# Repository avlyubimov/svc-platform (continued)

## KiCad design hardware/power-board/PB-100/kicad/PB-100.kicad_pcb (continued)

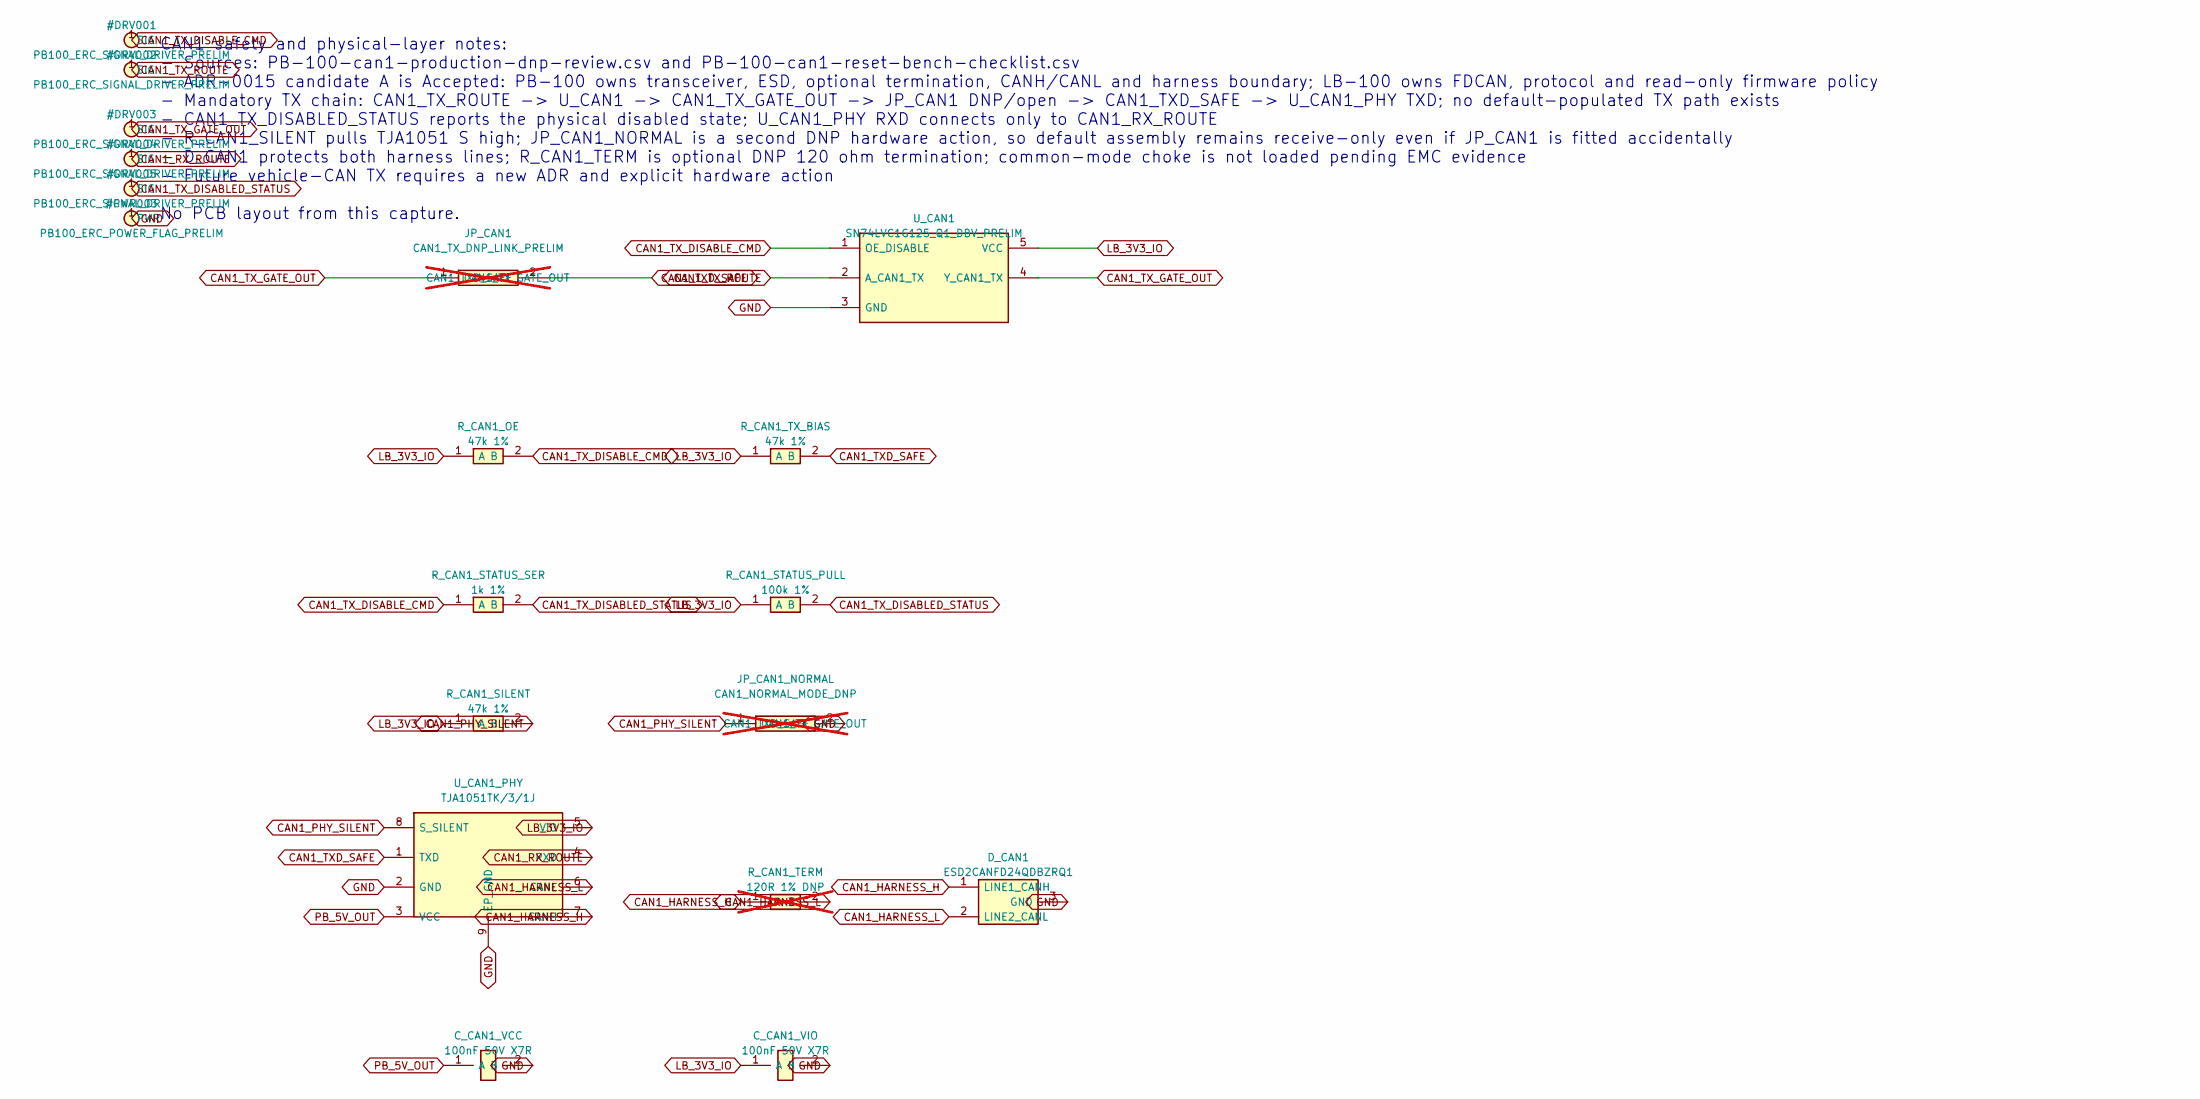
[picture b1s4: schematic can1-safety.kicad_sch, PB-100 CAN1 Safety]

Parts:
C_CAN1_VCC, C_CAN1_VIO: 100nF 50V X7R; C0402
D_CAN1: ESD2CANFD24QDBZRQ1; SOT-23-3_DBZ_TI
JP_CAN1: CAN1_TX_DNP_LINK_PRELIM; R0603_DNP_LINK_1608Metric; not fitted
JP_CAN1_NORMAL: CAN1_NORMAL_MODE_DNP; R0603_DNP_LINK_1608Metric; not fitted
R_CAN1_OE, R_CAN1_SILENT, R_CAN1_TX_BIAS: 47k 1%; R0402
R_CAN1_STATUS_PULL: 100k 1%; R0402
R_CAN1_STATUS_SER: 1k 1%; R0402
R_CAN1_TERM: 120R 1% DNP; R0603_DNP_LINK_1608Metric; not fitted
U_CAN1: SN74LVC1G125_Q1_DBV_PRELIM; SOT-23-5_DBV_TI
U_CAN1_PHY: TJA1051TK/3/1J; HVSON-8_L3.0-W3.0-P0.65-BL-EP

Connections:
CAN1_HARNESS_H: D_CAN1.1 (LINE1_CANH), R_CAN1_TERM.1 (A), U_CAN1_PHY.7 (CANH)
CAN1_HARNESS_L: D_CAN1.2 (LINE2_CANL), R_CAN1_TERM.2 (B), U_CAN1_PHY.6 (CANL)
CAN1_PHY_SILENT: JP_CAN1_NORMAL.1 (CAN1_TX_GATE_OUT), R_CAN1_SILENT.2 (B), U_CAN1_PHY.8 (S_SILENT)
CAN1_TXD_SAFE: JP_CAN1.2 (CAN1_TXD_SAFE), R_CAN1_TX_BIAS.2 (B), U_CAN1_PHY.1 (TXD)
LB_3V3_IO: C_CAN1_VIO.1 (A), R_CAN1_OE.1 (A), R_CAN1_SILENT.1 (A), R_CAN1_STATUS_PULL.1 (A), R_CAN1_TX_BIAS.1 (A), U_CAN1.5 (VCC), U_CAN1_PHY.5 (VIO); also elsewhere on the board
PB_5V_OUT: C_CAN1_VCC.1 (A), U_CAN1_PHY.3 (VCC); also elsewhere on the board

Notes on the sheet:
CAN1 safety and physical-layer notes: - Sources: PB-100-can1-production-dnp-review.csv and PB-100-can1-reset-bench-checklist.csv - ADR-0015 candidate A is Accepted: PB-100 owns transceiver, ESD, optional termination, CANH/CANL and harness boundary; LB-100 owns FDCAN, protocol and read-only firmware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

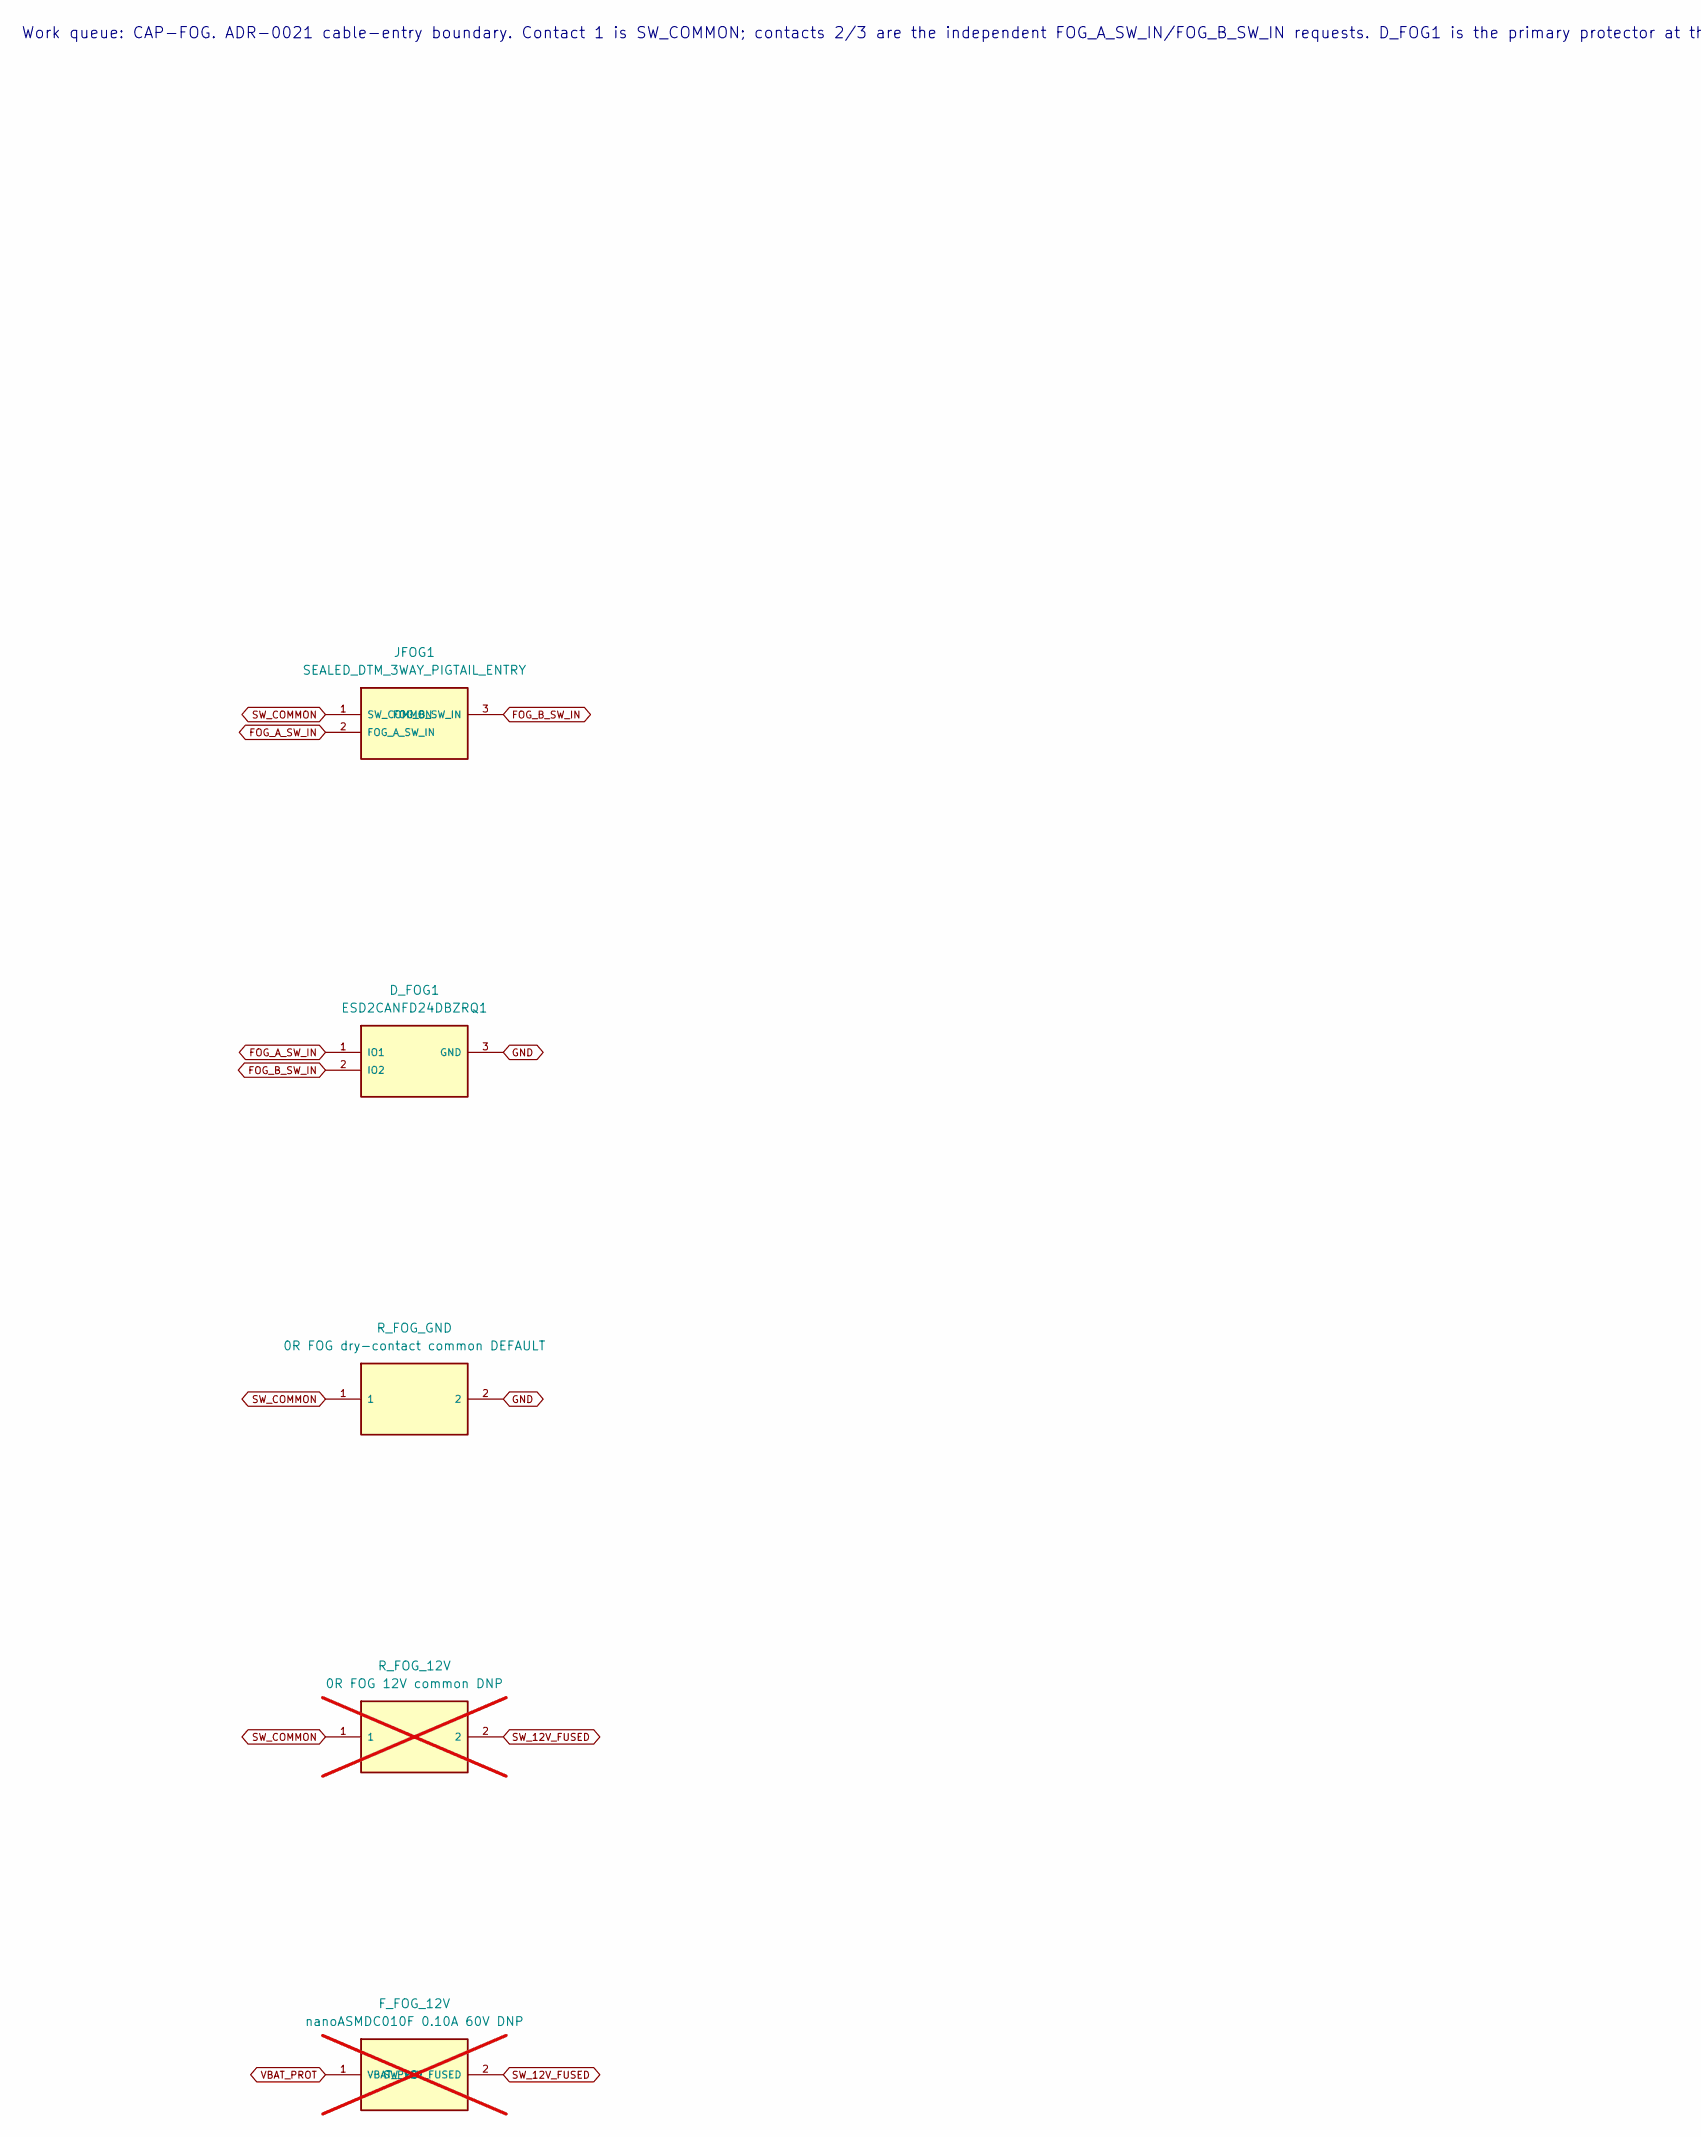
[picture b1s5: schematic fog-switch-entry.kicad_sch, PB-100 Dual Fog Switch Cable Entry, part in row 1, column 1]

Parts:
D_FOG1: ESD2CANFD24DBZRQ1; SOT-23-3_DBZ_TI
F_FOG_12V: nanoASMDC010F 0.10A 60V DNP; PPTC_1206_3216Metric; not fitted
JFOG1: SEALED_DTM_3WAY_PIGTAIL_ENTRY; FOG_PIGTAIL_1x03_P3.50mm
R_FOG_12V: 0R FOG 12V common DNP; R0603_DNP_LINK_1608Metric; not fitted
R_FOG_GND: 0R FOG dry-contact common DEFAULT; R0603_DNP_LINK_1608Metric

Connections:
SW_12V_FUSED: F_FOG_12V.2 (SW_12V_FUSED), R_FOG_12V.2
SW_COMMON: JFOG1.1 (SW_COMMON), R_FOG_12V.1, R_FOG_GND.1
VBAT_PROT: F_FOG_12V.1 (VBAT_PROT); also elsewhere on the board

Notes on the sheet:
Work queue: CAP-FOG. ADR-0021 cable-entry boundary. Contact 1 is SW_COMMON; contacts 2/3 are the independent FOG_A_SW_IN/FOG_B_SW_IN requests. D_FOG1 is the primary protector at the PB entry. R_FOG_GND is fitted for the default dry-contact assembly. R_FOG_12V and F_FOG_12V are mutually exclusive DN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

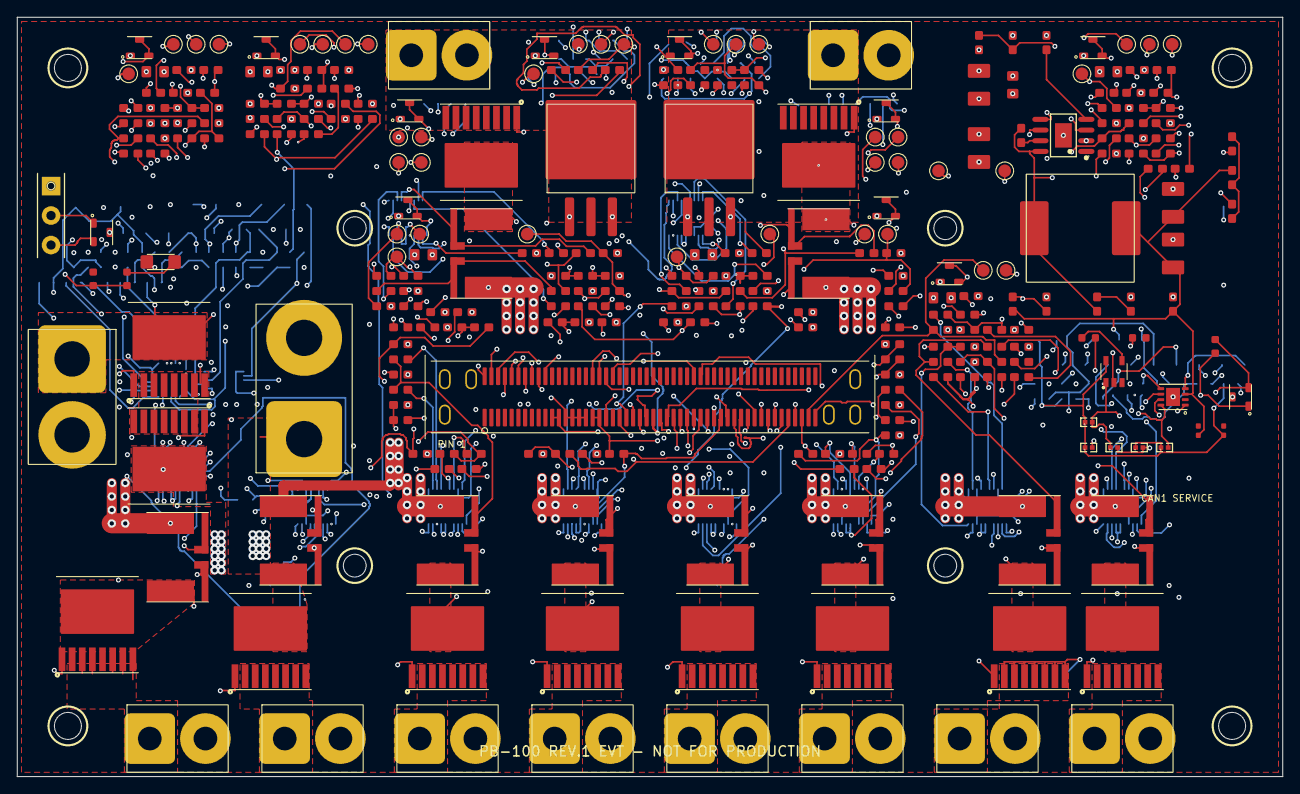
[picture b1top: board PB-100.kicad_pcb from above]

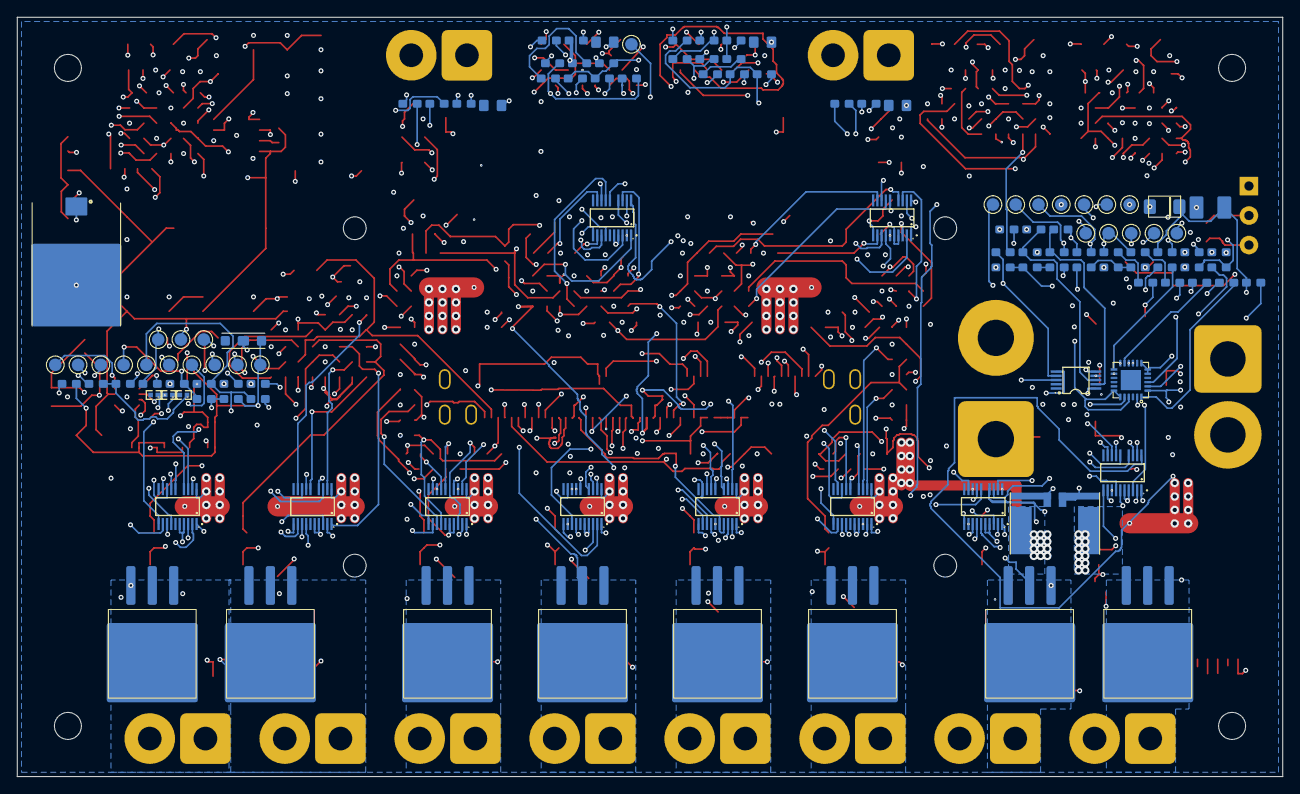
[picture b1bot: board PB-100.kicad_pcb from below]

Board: 8 copper layers, 150.0 x 90.0 mm, 422 parts (118 on the bottom side), 260 nets.

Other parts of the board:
H1, H2, H3, H4: LOCAL M3 NPTH; MountingHole_3.2mm
H5, H6, H7, H8: STACK M2.5 NPTH; MountingHole_2.7mm

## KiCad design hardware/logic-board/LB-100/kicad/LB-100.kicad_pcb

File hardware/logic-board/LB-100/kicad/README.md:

# LB-100 KiCad Project

Status: `EVT-FAB-AUTHORIZED`; connectivity-complete six-layer Rev.1 EVT layout

This directory contains the reviewed value-bearing LB-100 schematic,
project-local libraries and deterministically generated PCB.

The controlled `LB-100.kicad_pcb` contains all 104 schematic footprints, eight mounting
holes, the 100 mm x 70 mm outline, 2,274 routed segments, 409 standard
0.50/0.30 mm through vias and four GND zones. KiCad 10.0.4 refill DRC reports
zero errors and zero unconnected items; parity contains only H1-H8. Five
non-assembly pads provide E73 SWDIO, SWDCLK, reset, switched target reference
and GND recovery access.

The six-layer stack model is JLCPCB `JLC06161H-3313`. In2.Cu and In4.Cu are
solid GND reference planes, In1.Cu and In3.Cu carry signals, and the E73 rule
area covers every copper layer. The routing manifest is the source for board
generation; do not hand-edit generated copper.

Validation with KiCad 10.0.4:

```sh
python3 tools/validate_lb100_layout.py
```

The validator checks deterministic generation, schematic parity, route/via
counts, standard through-via construction, reference-plane exclusivity, USB
geometry and analytical impedance regression, VEML7700 disposition, the
six-layer E73 keepout and the exact reviewed non-electrical warning set.

Any EVT fabrication package must remain LB-only, marked
`LB-100 REV.1 EVT - NOT FOR PRODUCTION`, and must pass the supplier stackup,
impedance and DFM preflight before payment. PB-100 and the combined three-board
order remain `NO-GO`. Authorized LB manufacturing outputs are segregated under
`../manufacturing/evt-rev1/`; no assembly outputs are authorized.

## Source documents

- `../LB-100-layout-progress.md`
- `../LB-100-evt-fab-review-2026-07-22.md`
- `../LB-100-e73-antenna-keepout.md`
- `../LB-100-pcb-layout-start-checklist.csv`
- `../../../../production/board-order/three_board_layout_rules.md`
- `../../../../docs/adr/ADR-0014-lb-fb-baseline-requirements.md`

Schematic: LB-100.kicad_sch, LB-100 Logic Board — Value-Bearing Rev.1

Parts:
C1: 1uF 10V X7R; R_C_0603_1608Metric
C2, C4, C28: 1uF 6.3V X7R; R_C_0603_1608Metric
C3: 10uF 6.3V X7R; R_C_0805_2012Metric
C5, C8, C15, C16, C17, C18, C19, C20, C21, C22, C23, C24, C25, C26, C27, C29, C30: 100nF 6.3V X7R; R_C_0603_1608Metric
C6, C7: 2.2uF 6.3V X7R; R_C_0603_1608Metric
C9, C10: 18pF 50V C0G; R_C_0603_1608Metric
C11, C12: 8.2pF 50V C0G; R_C_0603_1608Metric
C13, C14: 1nF 50V C0G; R_C_0603_1608Metric
C31: 100nF 6.3V X7R BMI270 VDDIO; R_C_0603_1608Metric
C32: 100nF 6.3V X7R U15; R_C_0603_1608Metric
C33: 100nF 6.3V X7R U16; R_C_0603_1608Metric
C34: 100nF 6.3V X7R U17; R_C_0603_1608Metric
C35: 47nF 50V X7R FOG_A filter; R_C_0603_1608Metric
C36: 47nF 50V X7R FOG_B filter; R_C_0603_1608Metric
C37: 100nF 6.3V X7R U18; R_C_0603_1608Metric
C38: 100nF 6.3V X7R U19; R_C_0603_1608Metric
D19, D20: BZT52H-B4V3-Q; SOD-123F_L2.6-W1.6
FB1: 600R@100MHz 0.2A; R_C_0603_1608Metric
JBT1: BACKUP_BATTERY_2V3_TO_3V6_DNP; PinHeader_1x02_P2.54mm_Vertical; not fitted
JDBG1: SWD_2x3_1.27mm; PinHeader_2x03_P1.27mm_Vertical
JFB1: AFC07-S24ECA-00; FPC-SMD_AFC07-S24ECA-00
JPB1: FX18-100S-0.8SV10; FX18-100S-0.8SV10_Hirose
JSD1: TF-015; TF-SMD_TF-015
Q18, Q19: BC847BQ-7-F 12V OPTION; SOT-23-3_DBZ_TI; not fitted
R1: 100k 1%; R_C_0603_1608Metric
R2, R3, R13, R14, R15, R16: 0R; R_C_0603_1608Metric
R4, R5, R12: 10k 1%; R_C_0603_1608Metric
R6, R7: 2.2k 1%; R_C_0603_1608Metric
R8: 4.7k 1%; R_C_0603_1608Metric
R9: 10k 1% switched reset pull-up; R_C_0603_1608Metric
R10, R11: 47k 1%; R_C_0603_1608Metric
R17: 0R single-point analog return; R_C_0603_1608Metric
R18, R19: 22k 1% switched UART idle clamp; R_C_0603_1608Metric
R20, R22: 100k 1% MCU UART idle pull-up; R_C_0603_1608Metric
R21: 100k 1% reset default assert; R_C_0603_1608Metric
R23: 4.7k 1% FOG_A dry-contact series; R_C_0603_1608Metric
R24: 47k 1% FOG_A 12V base DNP; R_C_0603_1608Metric; not fitted
R25: 100k 1% FOG_A base pull-down DNP; R_C_0603_1608Metric; not fitted
R26: 47k 1% FOG_A pull-up; R_C_0603_1608Metric
R27: 4.7k 1% FOG_B dry-contact series; R_C_0603_1608Metric
R28: 47k 1% FOG_B 12V base DNP; R_C_0603_1608Metric; not fitted
R29: 100k 1% FOG_B base pull-down DNP; R_C_0603_1608Metric; not fitted
R30: 47k 1% FOG_B pull-up; R_C_0603_1608Metric
TP1: E73_SWDIO; TestPoint_SMD_1.2mm
TP2: E73_SWDCLK; TestPoint_SMD_1.2mm
TP3: BLE_RESET_N; TestPoint_SMD_1.2mm
TP4: RADIO_SENSOR_3V3; TestPoint_SMD_1.2mm
TP5: GND; TestPoint_SMD_1.2mm
U1: STM32H563VIT6; LQFP-100_L14.0-W14.0-P0.50-LS16.0-BL
U2: XC6220B331MR-G; SOT-25_L3.0-W1.6-P0.95-LS2.8-TL
U3: TCA9539QPWRQ1; TSSOP-24_4.4x7.8mm_P0.65mm
U4: TJA1051TK/3,118; HVSON-8_L3.0-W3.0-P0.65-BL-EP; not fitted
U5: TJA1021T/20/CM,118; SOIC-8_L4.9-W3.9-P1.27-LS6.0-BL; not fitted
U6: SP3485EN-L/TR; SOIC-8_L5.0-W4.0-P1.27-LS6.0-BL; not fitted
U7: E73-2G4M08S1C; WIRELM-SMD_E73-2G4M08S1C
U8: FM24CL64B-GTR; SOIC-8_L4.9-W3.9-P1.27-LS6.0-BL
U9: DS3231MZ+TRL; SOIC-8_L4.9-W3.9-P1.27-LS6.0-BL
U10: BMI270; LGA-14_L3.0-W2.5-P0.50-BR
U11: VEML7700-TT; SENSOR-SMD_EML7700-TT
U12, U13: TPS22918TDBVRQ1; SOT-23-6_L2.9-W1.6-P0.95-LS2.8-BL
U14, U18, U19: SN74LVC1G17QDBVRQ1; SOT-25_L3.0-W1.6-P0.95-LS2.8-TL
U15, U16, U17: SN74LVC1G125QDBVRQ1; SOT-25_L3.0-W1.6-P0.95-LS2.8-TL
Y1: ABM8AIG-25.000MHZ-12-2Z-T3; Crystal_SMD_3225-4Pin
Y2: ABS07AIG-32.768kHz-7-T; Crystal_SMD_3215-2Pin

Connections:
ADC_REF: C28.1, C29.1, JPB1.66 (ADC_REF), R16.2, U1.21 (VREF+)
AGND: C4.2, C5.2, C28.2, C29.2, JPB1.11 (AGND), JPB1.12 (AGND), R17.1, U1.19 (VSSA), U1.20 (VREF-)
BACKUP_AON: JBT1.1 (BACKUP_AON), U9.6 (VBAT)
BLE_RESET_N: R9.2, TP3.1 (BLE_RESET_N), U7.26 (RESET), U17.4 (Y)
BLE_RESET_N_MCU: R21.1, U1.97 (PE0), U17.2 (A)
BLE_UART_RX_MODULE: R18.1, U7.22 (P0.07), U15.4 (Y)
BLE_UART_TX_MODULE: R19.1, U7.20 (P0.12), U16.2 (A)
BOOT0: R5.1, U1.94 (BOOT0)
CAN1_RX_ROUTE: JPB1.69 (CAN1_RX_ROUTE), U1.95 (PB8)
CAN1_TX_DISABLED_STATUS: JPB1.68 (CAN1_TX_DISABLED_STATUS), U1.58 (PD11)
CAN1_TX_DISABLE_CMD: JPB1.67 (CAN1_TX_DISABLE_CMD), U1.85 (PD4)
CAN1_TX_ROUTE: JPB1.70 (CAN1_TX_ROUTE), U1.96 (PB9)
CAN2_RX_ROUTE: JPB1.71 (CAN2_RX_ROUTE), U1.51 (PB12), U4.4 (RXD)
CAN2_TX_ROUTE: JPB1.72 (CAN2_TX_ROUTE), U1.52 (PB13), U4.1 (TXD)
CH_LED_1: JFB1.10 (CH_LED_1), U3.4 (P00)
CH_LED_2: JFB1.11 (CH_LED_2), U3.5 (P01)
CH_LED_3: JFB1.12 (CH_LED_3), U3.6 (P02)
CH_LED_4: JFB1.13 (CH_LED_4), U3.7 (P03)
CH_LED_5: JFB1.14 (CH_LED_5), U3.8 (P04)
CH_LED_6: JFB1.15 (CH_LED_6), U3.9 (P05)
CH_LED_7: JFB1.16 (CH_LED_7), U3.10 (P06)
CH_LED_8: JFB1.17 (CH_LED_8), U3.11 (P07)
CH_LED_9: JFB1.18 (CH_LED_9), U3.13 (P10)
CH_LED_10: JFB1.19 (CH_LED_10), U3.14 (P11)
E73_SWDCLK: TP2.1 (E73_SWDCLK), U7.39 (SWDCLK)
E73_SWDIO: TP1.1 (E73_SWDIO), U7.37 (SWDIO)
EXT_5V_EN: JPB1.84 (EXT_5V_EN), U1.69 (PA10)
EXT_ADC1: JPB1.80 (EXT_ADC1), U1.64 (PC7)
EXT_ADC2: JPB1.81 (EXT_ADC2), U1.65 (PC8)
FB_3V3_OR_IO: JFB1.2 (FB_3V3_OR_IO), R3.2
FOG_A_12V_BASE: Q18.1 (B), R24.2, R25.1
FOG_A_FILTERED: C35.1, D19.1 (K), Q18.3 (C), R23.2, R26.2, U18.2 (A)
FOG_A_SW_IN: JPB1.82 (FOG_A_SW_IN), R23.1, R24.1
FOG_A_SW_IN_MCU: U1.67 (PA8), U18.4 (Y)
FOG_B_12V_BASE: Q19.1 (B), R28.2, R29.1
FOG_B_FILTERED: C36.1, D20.1 (K), Q19.3 (C), R27.2, R30.2, U19.2 (A)
FOG_B_SW_IN: JPB1.83 (FOG_B_SW_IN), R27.1, R28.1
FOG_B_SW_IN_MCU: U1.68 (PA9), U19.4 (Y)
GND: C1.2, C2.2, C3.2, C6.2, C7.2, C8.2, C9.2, C10.2, C11.2, C12.2, C13.2, C14.2, C15.2, C16.2, C17.2, C18.2, C19.2, C20.2, C21.2, C22.2, C23.2, C24.2, C25.2, C26.2, C27.2, C30.2, C31.2, C32.2, C33.2, C34.2, C35.2, C36.2, C37.2, C38.2, D19.2 (A), D20.2 (A), JBT1.2 (GND), JDBG1.3 (GND), JDBG1.5 (GND), JFB1.1 (GND), JFB1.3 (GND), JFB1.25 (SHIELD_A), JFB1.26 (SHIELD_B), JPB1.1 (GND), JPB1.2 (GND), JPB1.3 (GND), JPB1.4 (GND), JPB1.5 (GND), JPB1.6 (GND), JPB1.7 (GND), JPB1.8 (GND), JPB1.9 (GND), JPB1.10 (GND), JPB1.MF_A_PIN1_51_END, JPB1.MF_A_PIN50_100_END, JPB1.MF_B_PIN1_51_END, JPB1.MF_B_PIN50_100_END, JSD1.6 (VSS), JSD1.10 (SHELL1), JSD1.11 (SHELL2), JSD1.12 (SHELL3), JSD1.13 (SHELL4), Q18.2 (E), Q19.2 (E), R1.2, R5.2, R17.2, R21.2, R25.2, R29.2, TP5.1 (GND), U1.10 (VSS), U1.27 (VSS), U1.49 (VSS), U1.74 (VSS), U1.99 (VSS), U2.2 (VSS), U3.2 (A1), U3.12 (GND), U3.21 (A0), U4.2 (GND), U4.9 (EP), U5.2 (SLP_N), U5.5 (GND), U6.5 (GND), U7.5 (GND), U7.21 (GND), U7.24 (GND), U8.1 (A0), U8.2 (A1), U8.3 (A2), U8.4 (VSS), U8.7 (WP), U9.5 (GND), U10.1 (SDO), U10.6 (GNDIO), U10.7 (GND), U11.3 (GND), U12.2 (GND), U13.2 (GND), U14.3 (GND), U15.1 (OE_N), U15.3 (GND), U16.1 (OE_N), U16.3 (GND), U17.1 (OE_N), U17.3 (GND), U18.3 (GND), U19.3 (GND), Y1.2 (GND1), Y1.4 (GND2)
IIN_SENSE: JPB1.52 (IIN_SENSE), U1.32 (PA7)
IMU_INT1: U3.18 (P15), U10.4 (INT1)
IOX_INT_N: R8.2, U1.54 (PB15), U3.1 (INT_N)
LB_3V3_ANALOG: C4.1, C5.1, FB1.2, R16.1, U1.22 (VDDA)
LB_3V3_IO: C30.1, C31.1, C37.1, C38.1, JPB1.17 (LB_3V3_IO), JPB1.18 (LB_3V3_IO), R2.2, R6.1, R7.1, R26.1, R30.1, U10.5 (VDDIO), U10.12 (CSB), U11.2 (VDD), U14.5 (VCC), U18.5 (VCC), U19.5 (VCC)
LB_3V3_MAIN: C2.1, C3.1, C15.1, C16.1, C17.1, C18.1, C19.1, C20.1, C21.1, FB1.1, JDBG1.1 (VTREF), R2.1, R3.1, R4.1, R8.1, R20.1, R22.1, U1.6 (VBAT), U1.11 (VDD), U1.28 (VDD), U1.50 (VDD), U1.73 (VDDUSB), U1.75 (VDD), U1.100 (VDD), U2.5 (VOUT), U3.24 (VCC), U4.5 (VIO), U4.8 (S), U5.3 (WAKE_N), U6.8 (VCC), U8.8 (VDD), U9.2 (VCC), U12.1 (VIN), U13.1 (VIN)
LIN_RX: JPB1.74 (LIN_RX), U1.87 (PD6), U5.1 (RXD)
LIN_TX: JPB1.73 (LIN_TX), U1.86 (PD5), U5.4 (TXD)
MCU_HSE_IN: C9.1, U1.12 (PH0-OSC_IN), Y1.1 (XIN)
MCU_HSE_OUT: C10.1, U1.13 (PH1-OSC_OUT), Y1.3 (XOUT)
MCU_LSE_IN: C11.1, U1.8 (PC14-OSC32_IN), Y2.1 (XIN)
MCU_LSE_OUT: C12.1, U1.9 (PC15-OSC32_OUT), Y2.2 (XOUT)
MICROSD_3V3: C26.1, C27.1, JSD1.4 (VDD), R10.1, R11.1, R12.1, U12.5 (QOD), U12.6 (VOUT)
MICROSD_3V3_CT: C13.1, U12.4 (CT)
MICROSD_CARD_DETECT: JSD1.9 (CARD_DETECT), U3.17 (P14)
MICROSD_CS_N: JSD1.2 (CD_DAT3), R12.2, U1.80 (PC12)
MICROSD_DAT1: JSD1.8 (DAT1), R10.2
MICROSD_DAT2: JSD1.1 (DAT2), R11.2
MICROSD_PWR_EN: U1.81 (PD0), U12.3 (ON)
NRST: C8.1, R4.2, R15.1, U1.14 (NRST), U3.3 (RESET_N), U9.4 (RST_N)
OLED_RST_OR_INT_DNP: JFB1.24 (OLED_RST_OR_INT_DNP), U3.20 (P17)
OLED_SCL: JFB1.22 (OLED_SCL), R13.2
OLED_SDA: JFB1.23 (OLED_SDA), R14.2
OUT1_CTL: JPB1.21 (OUT1_CTL), U1.4 (PE5)
OUT1_FLT: JPB1.31 (OUT1_FLT), U1.1 (PE2)
OUT1_IMON: JPB1.41 (OUT1_IMON), U1.15 (PC0)
OUT2_CTL: JPB1.22 (OUT2_CTL), U1.5 (PE6)
OUT2_FLT: JPB1.32 (OUT2_FLT), U1.2 (PE3)
OUT2_IMON: JPB1.42 (OUT2_IMON), U1.16 (PC1)
OUT3_CTL: JPB1.23 (OUT3_CTL), U1.40 (PE9)
OUT3_FLT: JPB1.33 (OUT3_FLT), U1.3 (PE4)
OUT3_IMON: JPB1.43 (OUT3_IMON), U1.17 (PC2)
OUT4_CTL: JPB1.24 (OUT4_CTL), U1.42 (PE11)
OUT4_FLT: JPB1.34 (OUT4_FLT), U1.38 (PE7)
OUT4_IMON: JPB1.44 (OUT4_IMON), U1.18 (PC3)
OUT5_CTL: JPB1.25 (OUT5_CTL), U1.44 (PE13)
OUT5_FLT: JPB1.35 (OUT5_FLT), U1.39 (PE8)
OUT5_IMON: JPB1.45 (OUT5_IMON), U1.23 (PA0)
OUT6_CTL: JPB1.26 (OUT6_CTL), U1.45 (PE14)
OUT6_FLT: JPB1.36 (OUT6_FLT), U1.41 (PE10)
OUT6_IMON: JPB1.46 (OUT6_IMON), U1.24 (PA1)
OUT7_CTL: JPB1.27 (OUT7_CTL), U1.59 (PD12)
OUT7_FLT: JPB1.37 (OUT7_FLT), U1.43 (PE12)
OUT7_IMON: JPB1.47 (OUT7_IMON), U1.25 (PA2)
OUT8_CTL: JPB1.28 (OUT8_CTL), U1.60 (PD13)
OUT8_FLT: JPB1.38 (OUT8_FLT), U1.46 (PE15)
OUT8_IMON: JPB1.48 (OUT8_IMON), U1.26 (PA3)
OUT9_CTL: JPB1.29 (OUT9_CTL), U1.61 (PD14)
OUT9_FLT: JPB1.39 (OUT9_FLT), U1.63 (PC6)
OUT9_IMON: JPB1.49 (OUT9_IMON), U1.29 (PA4)
OUT10_CTL: JPB1.30 (OUT10_CTL), U1.62 (PD15)
OUT10_FLT: JPB1.40 (OUT10_FLT), U1.66 (PC9)
OUT10_IMON: JPB1.50 (OUT10_IMON), U1.30 (PA5)
PB_5V_OUT: C1.1, JPB1.13 (PB_5V_OUT), JPB1.14 (PB_5V_OUT), JPB1.15 (PB_5V_OUT), JPB1.16 (PB_5V_OUT), U2.1 (VIN), U4.3 (VCC)
PB_FAULT: JPB1.56 (PB_FAULT), U1.84 (PD3)
PB_I2C_INT: JPB1.59 (PB_I2C_INT), U1.47 (PB10)
PB_I2C_SCL: JPB1.57 (PB_I2C_SCL), R6.2, R13.1, U1.92 (PB6), U3.22 (SCL), U8.6 (SCL), U9.8 (SCL), U10.13 (SCL), U11.1 (SCL)
PB_I2C_SDA: JPB1.58 (PB_I2C_SDA), R7.2, R14.1, U1.93 (PB7), U3.23 (SDA), U8.5 (SDA), U9.7 (SDA), U10.14 (SDA), U11.4 (SDA)
PB_ID_ADC: JPB1.60 (PB_ID_ADC), U1.36 (PB1)
PB_PWR_GOOD: JPB1.19 (PB_PWR_GOOD), R1.1, U1.83 (PD2), U2.3 (CE)
PB_SPI_CS0: JPB1.64 (PB_SPI_CS0), U1.77 (PA15)
PB_SPI_CS1: JPB1.65 (PB_SPI_CS1), U1.37 (PB2)
PB_SPI_MISO: JPB1.62 (PB_SPI_MISO), JSD1.7 (DAT0), U1.90 (PB4)
PB_SPI_MOSI: JPB1.63 (PB_SPI_MOSI), JSD1.3 (CMD), U1.91 (PB5)
PB_SPI_SCK: JDBG1.6 (SWO), JPB1.61 (PB_SPI_SCK), JSD1.5 (CLK), U1.89 (PB3-SWO)
PB_WAKE_REQ: JPB1.20 (PB_WAKE_REQ), U1.7 (PC13)
RADIO_SENSOR_3V3: C22.1, C23.1, C24.1, C25.1, C32.1, C33.1, C34.1, R9.1, R18.2, R19.2, TP4.1 (RADIO_SENSOR_3V3), U7.19 (VCC), U10.8 (VDD), U13.5 (QOD), U13.6 (VOUT), U15.5 (VCC), U16.5 (VCC), U17.5 (VCC)
RADIO_SENSOR_3V3_CT: C14.1, U13.4 (CT)
RADIO_SENSOR_EN: U1.82 (PD1), U13.3 (ON)
RESET_BTN: JFB1.21 (RESET_BTN), R15.2
RS485_DE: JPB1.75 (RS485_DE), U1.53 (PB14), U6.2 (RE_N), U6.3 (DE)
RS485_RX: JPB1.76 (RS485_RX), U1.56 (PD9), U6.1 (RO)
RS485_TX: JPB1.77 (RS485_TX), U1.55 (PD8), U6.4 (DI)
RTC_INT_N: U3.19 (P16), U9.3 (INT_SQW_N)
SERVICE_BTN: JFB1.20 (SERVICE_BTN), U3.16 (P13)
STATUS_RGB_DATA: JFB1.9 (STATUS_RGB_DATA), U1.88 (PD7)
SWCLK: JDBG1.4 (SWCLK), U1.76 (PA14-SWCLK)
SWDIO: JDBG1.2 (SWDIO), U1.72 (PA13-SWDIO)
TEMP_PCB: JPB1.53 (TEMP_PCB), U1.33 (PC4)
TEMP_PWR_A: JPB1.54 (TEMP_PWR_A), U1.34 (PC5)
TEMP_PWR_B: JPB1.55 (TEMP_PWR_B), U1.35 (PB0)
UART_RX: JPB1.79 (UART_RX), R20.2, U1.79 (PC11), U16.4 (Y)
UART_TX: JPB1.78 (UART_TX), R22.2, U1.78 (PC10), U15.2 (A)
USB_CC1: JFB1.6 (USB_CC1)
USB_CC2: JFB1.7 (USB_CC2)
USB_D_N: JFB1.5 (USB_D_N), U1.70 (PA11-USB_DM)
USB_D_P: JFB1.4 (USB_D_P), U1.71 (PA12-USB_DP)
USB_VBUS_DETECT_RAW: JFB1.8 (USB_VBUS_DETECT_RAW), U14.2 (A)
USB_VBUS_PRESENT: U1.57 (PD10), U14.4 (Y)
VBAT_SENSE: JPB1.51 (VBAT_SENSE), U1.31 (PA6)
VCAP1: C6.1, U1.48 (VCAP1)
VCAP2: C7.1, U1.98 (VCAP2)

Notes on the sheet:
LB-100 reviewed value-bearing Rev.1 capture. STM32H563VIT6 LQFP100; exact ST package positions; JPB1 100 signals plus four GND MF circuits; PB_5V_OUT 500 mA allocation with reviewed 229.2 mA sustained and 381.2 mA service-peak budgets including FB-100 worst-case indication; ADR-0015 CAN1 FDCAN/read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

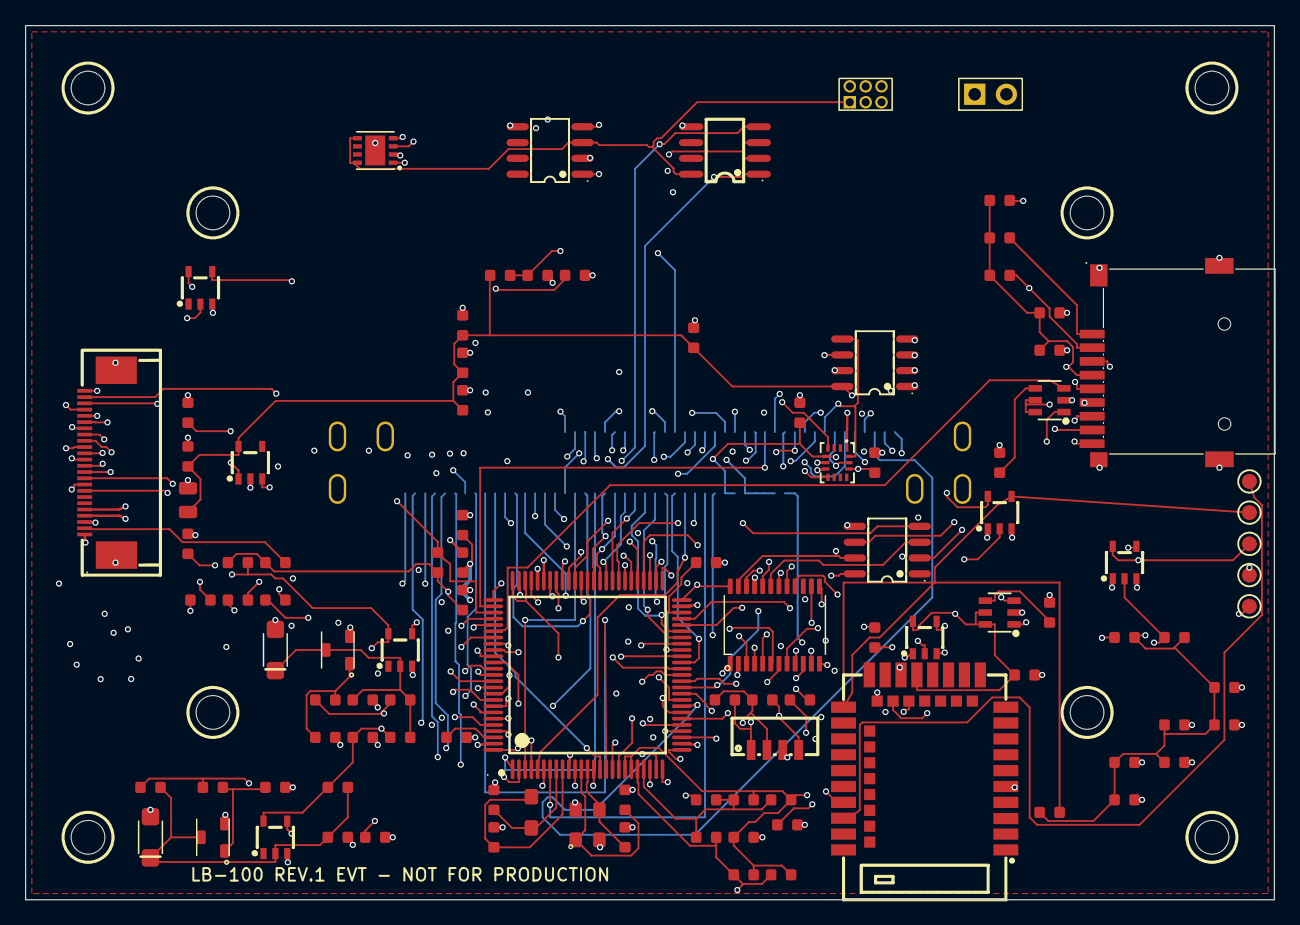
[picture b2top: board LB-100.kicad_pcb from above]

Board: 6 copper layers, 100.0 x 70.0 mm, 112 parts (1 on the bottom side), 129 nets.

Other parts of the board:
H1, H2, H3, H4: LOCAL M2.5 NPTH; MountingHole_2.7mm_M2.5
H5, H6, H7, H8: STACK M2.5 NPTH; MountingHole_2.7mm_M2.5

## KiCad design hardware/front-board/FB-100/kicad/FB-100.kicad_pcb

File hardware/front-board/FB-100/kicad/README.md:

# FB-100 KiCad Project

Status: `EVT-LAYOUT-AUTHORIZED`; connectivity routing complete; fab review open

This directory contains the reviewed value-bearing FB-100 KiCad schematic and
project-local symbol/footprint libraries.

The controlled `FB-100.kicad_pcb` placement and routing are generated from the frozen
44-component schematic and project-local footprints. Mechanical-envelope and
USB/no-back-power inputs are applied. The route manifest contains 457 segments,
48 vias and four filled GND zones with zero refilled DRC or unconnected findings.
USB stack geometry, analytical impedance/skew and transition return-via checks
are automated. Supplier field-solver confirmation, physical JFB1 cable/latch
fit, enclosure integration and final assembly DFM remain open. There are no
manufacturing outputs: Gerbers, drills, pick-place files, BOM/CPL order
packages, zipped fabrication packages, and board orders remain blocked until
the later prototype/production gates close.

Release boundary: no manufacturing outputs are authorized.

## Source Documents

- `../FB-100-requirements.md`
- `../FB-100-schematic-freeze-checklist.md`
- `../FB-100-pcb-layout-start-checklist.csv`
- `../FB-100-footprint-binding-inventory.csv`
- `../FB-100-footprint-binding-closeout.csv`
- `../FB-100-footprint-binding-closeout.md`
- `../FB-100-mechanical-envelope-inventory.csv`
- `../FB-100-mechanical-layout-inputs.csv`
- `../FB-100-usb-no-back-power-layout-rules.csv`
- `../FB-100-board-release-blocker-register.csv`
- `../../../../production/board-order/three_board_footprint_binding_status.csv`
- `../../../../production/board-order/three_board_mechanical_envelope_status.csv`
- `../../../logic-board/LB-100/LB-100-requirements.md`
- `../../../../docs/adr/ADR-0014-lb-fb-baseline-requirements.md`

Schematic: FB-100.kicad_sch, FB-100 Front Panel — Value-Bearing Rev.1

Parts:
C1: 100nF 16V X7R 10%; R_C_0603_1608Metric
C2: 1nF 1kV C0G; R_C_0603_1608Metric
C3, C4, C5: 1uF 6.3V X7R; R_C_0603_1608Metric
C6, C7: 100nF 6.3V X7R; R_C_0603_1608Metric
D1: USBLC6-2SC6; SOT-23-6_L2.9-W1.6-P0.95-LS2.8-BL
D2: 19-237/R6GHBHC-A01/2T; LED-ARRAY-SMD_4P-L1.6-W1.6-BL_1
D3, D4, D5, D6, D7, D8, D9, D10, D11, D12: KT-0805Y; LED0805-R-RD
J1: USB4105-GF-A; TYPE-C-SMD_SBC-160S1A-20-S412
J2: SSD1306_I2C_MODULE_DNP; PinHeader_1x04_P2.54mm_Vertical; not fitted
JFB1: AFC07-S24ECA-00; FPC-SMD_AFC07-S24ECA-00
R1, R2, R3, R4, R5, R6, R7, R8, R9, R10: 1k 1%; R_C_0603_1608Metric
R11, R12: 5.1k 1%; R_C_0603_1608Metric
R13: 3.9k 1% current limit; R_C_0603_1608Metric
R14: 15k 1% defined pulldown; R_C_0603_1608Metric
R15: 1M 1%; R_C_0603_1608Metric
R16: 35.7k 1%; R_C_0603_1608Metric
R17, R18: 10k 1%; R_C_0603_1608Metric
R19: 100k 1%; R_C_0603_1608Metric
SW1: EVPBB4A9B000 SERVICE; KEY-SMD_L2.6-W1.6-P0.75-LS3.0
SW2: EVPBB4A9B000 RESET; KEY-SMD_L2.6-W1.6-P0.75-LS3.0
U1: LTC3212EDDB#TRPBF; DFN-12-1EP_2x3mm_P0.45mm

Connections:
CH_LED_1: D3.2 (K), JFB1.10 (CH_LED_1)
CH_LED_1_A: D3.1 (A), R1.2
CH_LED_2: D4.2 (K), JFB1.11 (CH_LED_2)
CH_LED_2_A: D4.1 (A), R2.2
CH_LED_3: D5.2 (K), JFB1.12 (CH_LED_3)
CH_LED_3_A: D5.1 (A), R3.2
CH_LED_4: D6.2 (K), JFB1.13 (CH_LED_4)
CH_LED_4_A: D6.1 (A), R4.2
CH_LED_5: D7.2 (K), JFB1.14 (CH_LED_5)
CH_LED_5_A: D7.1 (A), R5.2
CH_LED_6: D8.2 (K), JFB1.15 (CH_LED_6)
CH_LED_6_A: D8.1 (A), R6.2
CH_LED_7: D9.2 (K), JFB1.16 (CH_LED_7)
CH_LED_7_A: D9.1 (A), R7.2
CH_LED_8: D10.2 (K), JFB1.17 (CH_LED_8)
CH_LED_8_A: D10.1 (A), R8.2
CH_LED_9: D11.2 (K), JFB1.18 (CH_LED_9)
CH_LED_9_A: D11.1 (A), R9.2
CH_LED_10: D12.2 (K), JFB1.19 (CH_LED_10)
CH_LED_10_A: D12.1 (A), R10.2
FB_3V3_OR_IO: C3.1, J2.2 (VCC), JFB1.2 (FB_3V3_OR_IO), R1.1, R2.1, R3.1, R4.1, R5.1, R6.1, R7.1, R8.1, R9.1, R10.1, R17.1, R18.1, U1.4 (ISETB), U1.5 (ISETR), U1.12 (VIN)
GND: C1.2, C2.2, C3.2, C5.2, C6.2, C7.2, D1.2 (GND), J1.A1 (GND), J1.A12 (GND), J1.B1 (GND), J1.B12 (GND), J2.1 (GND), JFB1.1 (GND), JFB1.3 (GND), JFB1.25 (SHIELD_A), JFB1.26 (SHIELD_B), R11.2, R12.2, R14.2, R15.2, R16.2, R19.2, SW1.B, SW1.B1, SW2.B, SW2.B1, U1.10 (GND), U1.13 (EP)
OLED_RST_OR_INT_DNP: JFB1.24 (OLED_RST_OR_INT_DNP), R19.1
OLED_SCL: J2.3 (SCL), JFB1.22 (OLED_SCL)
OLED_SDA: J2.4 (SDA), JFB1.23 (OLED_SDA)
RESET_BTN: C7.1, JFB1.21 (RESET_BTN), R18.2, SW2.A, SW2.A1
RGB_B_K: D2.4 (BLUE_K), U1.9 (LEDB)
RGB_CM: C4.2, U1.11 (CM)
RGB_CP: C4.1, U1.1 (CP)
RGB_G_K: D2.3 (GREEN_K), U1.7 (LEDG)
RGB_ISETG: R16.1, U1.6 (ISETG)
RGB_LED_ANODE: C5.1, D2.1 (COMMON_ANODE), U1.2 (CPO)
RGB_R_K: D2.2 (RED_K), U1.8 (LEDR)
SERVICE_BTN: C6.1, JFB1.20 (SERVICE_BTN), R17.2, SW1.A, SW1.A1
STATUS_RGB_DATA: JFB1.9 (STATUS_RGB_DATA), U1.3 (LEDEN)
USB_CC1: J1.A5 (CC1), JFB1.6 (USB_CC1), R11.1
USB_CC2: J1.B5 (CC2), JFB1.7 (USB_CC2), R12.1
USB_D_N: D1.4 (I_O2_OUT), JFB1.5 (USB_D_N)
USB_D_N_CONN: D1.3 (I_O2_IN), J1.A7 (D-), J1.B7 (D-)
USB_D_P: D1.6 (I_O1_OUT), JFB1.4 (USB_D_P)
USB_D_P_CONN: D1.1 (I_O1_IN), J1.A6 (D+), J1.B6 (D+)
USB_SHIELD: C2.1, J1.1 (SHIELD1), J1.2 (SHIELD2), J1.3 (SHIELD3), J1.4 (SHIELD4), R15.1
USB_VBUS: D1.5 (VBUS), J1.A4 (VBUS), J1.A9 (VBUS), J1.B4 (VBUS), J1.B9 (VBUS), R13.1
USB_VBUS_DETECT_RAW: C1.1, JFB1.8 (USB_VBUS_DETECT_RAW), R13.2, R14.1

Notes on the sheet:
FB-100 reviewed value-bearing Rev.1 capture. USB-C is USB2 device-only with two 5.1k Rd resistors, USBLC6-2SC6 flow-through ESD, current-limited VBUS detect, and no connection from USB VBUS to FB_3V3_OR_IO. LTC3212 converts the approved STATUS_RGB_DATA single wire into three regulated cathode curre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

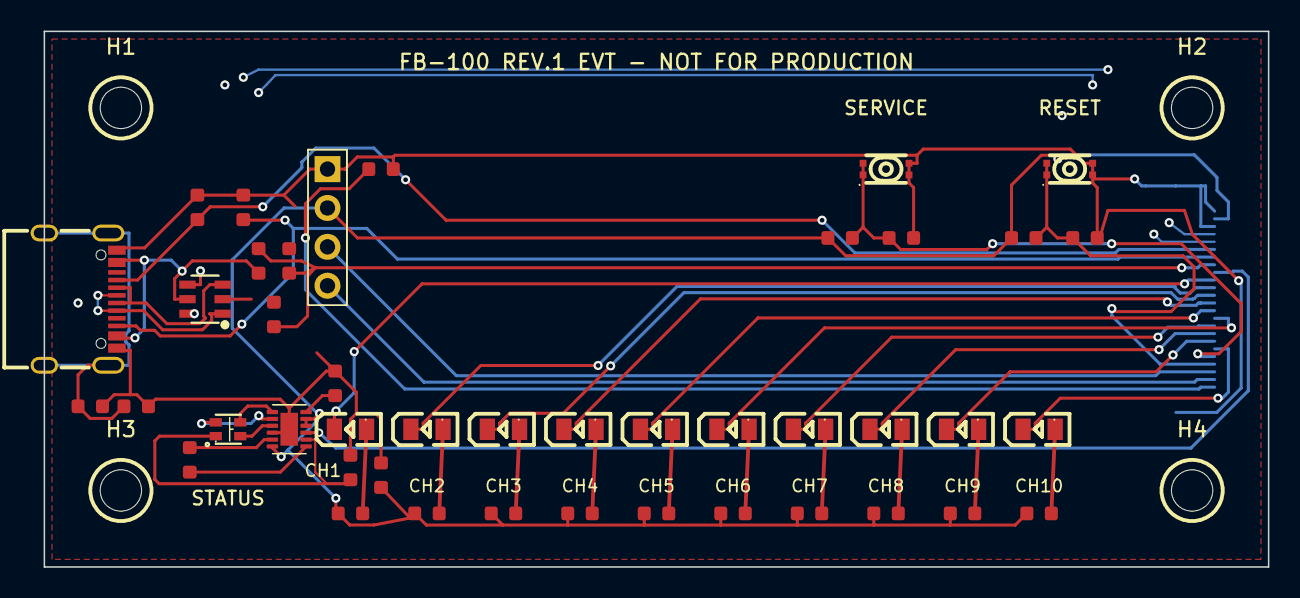
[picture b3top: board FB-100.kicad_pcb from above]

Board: 4 copper layers, 80.0 x 35.0 mm, 48 parts (1 on the bottom side), 44 nets.

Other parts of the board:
H1, H2, H3, H4: M2.5 NPTH; MountingHole_2.7mm_M2.5
